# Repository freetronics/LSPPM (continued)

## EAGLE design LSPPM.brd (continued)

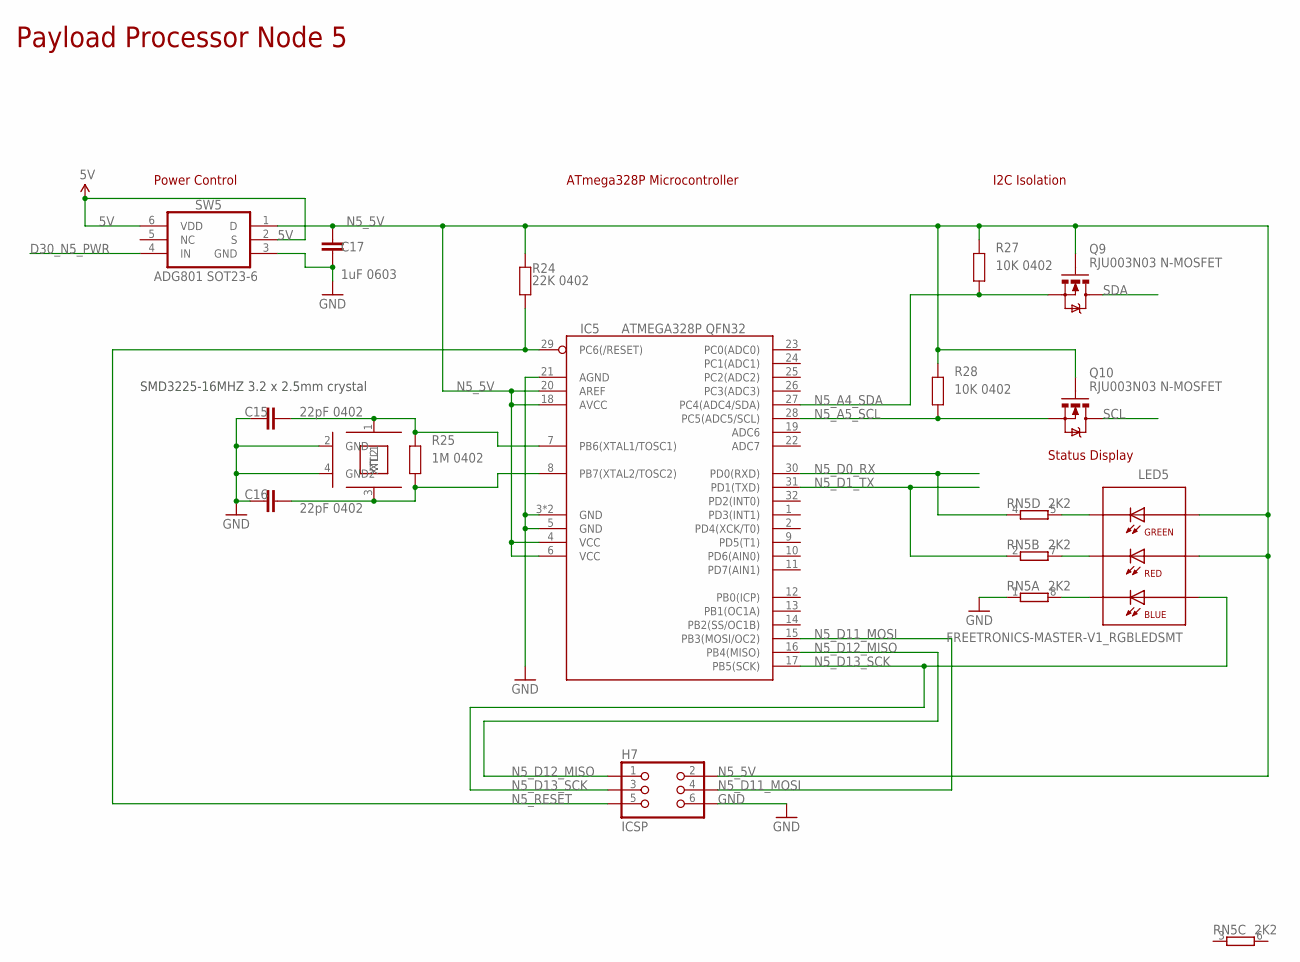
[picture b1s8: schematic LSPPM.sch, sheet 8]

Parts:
C15, C16: 22pF 0402; C0402
C17: 1uF 0603; C0603
H7: ICSP; M2X3-2MM
IC5: ATMEGA328P QFN32; MLF32
LED5: FREETRONICS-MASTER-V1_RGBLEDSMT; FREETRONICS-MASTER-V1_19-337
Q9, Q10: RJU003N03 N-MOSFET; SOT32-3
R24: 22K 0402; R0402
R25: 1M 0402; R0402
R27, R28: 10K 0402; R0402
RN5: 2K2; CAY16
SW5: ADG801 SOT23-6; SOT23-6
XTL5: SMD3225-16MHZ 3.2 x 2.5mm crystal; CRYSTAL-SMD-3X2

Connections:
5V: SW5.2 (S), SW5.6 (VDD); also elsewhere on the board
D30_N5_PWR: SW5.4 (IN); also elsewhere on the board
GND: C15.1, C16.1, C17.2, H7.6, IC5.3 (GND), IC5.5 (GND), IC5.21 (AGND), IC5.TGND (GND), RN5.1, SW5.3 (GND), XTL5.2 (GND), XTL5.4 (GND2); also elsewhere on the board
N5_5V: C17.1, H7.2, IC5.4 (VCC), IC5.6 (VCC), IC5.18 (AVCC), IC5.20 (AREF), LED5.5 (A-R), LED5.6 (A-G), Q9.1 (G), Q10.1 (G), R24.2, R27.2, R28.2, SW5.1 (D)
N5_A4_SDA: IC5.27 (PC4(ADC4/SDA)), Q9.2 (S), R27.1
N5_A5_SCL: IC5.28 (PC5(ADC5/SCL)), Q10.2 (S), R28.1
N5_D0_RX: IC5.30 (PD0(RXD)), RN5.4 (1); also elsewhere on the board
N5_D1_TX: IC5.31 (PD1(TXD)), RN5.2 (1); also elsewhere on the board
N5_D11_MOSI: H7.4, IC5.15 (PB3(MOSI/OC2))
N5_D12_MISO: H7.1, IC5.16 (PB4(MISO))
N5_D13_SCK: H7.3, IC5.17 (PB5(SCK)), LED5.4 (A-B)
N5_RESET: H7.5, IC5.29 (PC6(/RESET)), R24.1; also elsewhere on the board
unnamed: C16.2, IC5.8 (PB7(XTAL2/TOSC2)), R25.1, XTL5.3 (XTL2)
unnamed: C15.2, IC5.7 (PB6(XTAL1/TOSC1)), R25.2, XTL5.1 (XTL1)
unnamed: LED5.2 (C-R), RN5.7 (2)
unnamed: LED5.1 (C-B), RN5.8 (2)
unnamed: LED5.3 (C-G), RN5.5 (2)
SCL: Q10.3 (D); also elsewhere on the board
SDA: Q9.3 (D); also elsewhere on the board

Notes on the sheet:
Payload Processor Node 5
ATmega328P Microcontroller
I2C Isolation
Status Display
Power Control
SMD3225-16MHZ 3.2 x 2.5mm crystal

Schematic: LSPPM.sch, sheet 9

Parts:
C18, C19: 22pF 0402; C0402
C20: 1uF 0603; C0603
H8: ICSP; M2X3-2MM
IC6: ATMEGA328P QFN32; MLF32
LED6: FREETRONICS-MASTER-V1_RGBLEDSMT; FREETRONICS-MASTER-V1_19-337
Q13, Q14: RJU003N03 N-MOSFET; SOT32-3
R29: 22K 0402; R0402
R30: 1M 0402; R0402
R31, R34: 10K 0402; R0402
RN6: 2K2; CAY16
SW6: ADG801 SOT23-6; SOT23-6
XTL6: SMD3225-16MHZ 3.2 x 2.5mm crystal; CRYSTAL-SMD-3X2

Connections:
5V: SW6.2 (S), SW6.6 (VDD); also elsewhere on the board
D31_N6_PWR: SW6.4 (IN); also elsewhere on the board
GND: C18.1, C19.1, C20.2, H8.6, IC6.3 (GND), IC6.5 (GND), IC6.21 (AGND), IC6.TGND (GND), RN6.1, SW6.3 (GND), XTL6.2 (GND), XTL6.4 (GND2); also elsewhere on the board
N6_5V: C20.1, H8.2, IC6.4 (VCC), IC6.6 (VCC), IC6.18 (AVCC), IC6.20 (AREF), LED6.5 (A-R), LED6.6 (A-G), Q13.1 (G), Q14.1 (G), R29.2, R31.2, R34.2, SW6.1 (D)
N6_A4_SDA: IC6.27 (PC4(ADC4/SDA)), Q13.2 (S), R31.1
N6_A5_SCL: IC6.28 (PC5(ADC5/SCL)), Q14.2 (S), R34.1
N6_D0_RX: IC6.30 (PD0(RXD)), RN6.4 (1); also elsewhere on the board
N6_D1_TX: IC6.31 (PD1(TXD)), RN6.2 (1); also elsewhere on the board
N6_D11_MOSI: H8.4, IC6.15 (PB3(MOSI/OC2))
N6_D12_MISO: H8.1, IC6.16 (PB4(MISO))
N6_D13_SCK: H8.3, IC6.17 (PB5(SCK)), LED6.4 (A-B)
N6_RESET: H8.5, IC6.29 (PC6(/RESET)), R29.1; also elsewhere on the board
unnamed: C19.2, IC6.8 (PB7(XTAL2/TOSC2)), R30.1, XTL6.3 (XTL2)
unnamed: C18.2, IC6.7 (PB6(XTAL1/TOSC1)), R30.2, XTL6.1 (XTL1)
unnamed: LED6.2 (C-R), RN6.7 (2)
unnamed: LED6.1 (C-B), RN6.8 (2)
unnamed: LED6.3 (C-G), RN6.5 (2)
SCL: Q14.3 (D); also elsewhere on the board
SDA: Q13.3 (D); also elsewhere on the board

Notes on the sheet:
Payload Processor Node 6
ATmega328P Microcontroller
I2C Isolation
Status Display
Power Control
SMD3225-16MHZ 3.2 x 2.5mm crystal

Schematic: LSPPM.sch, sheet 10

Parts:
C21, C22: 22pF 0402; C0402
C23: 1uF 0603; C0603
H9: ICSP; M2X3-2MM
IC7: ATMEGA328P QFN32; MLF32
LED7: FREETRONICS-MASTER-V1_RGBLEDSMT; FREETRONICS-MASTER-V1_19-337
Q15, Q16: RJU003N03 N-MOSFET; SOT32-3
R35: 22K 0402; R0402
R36: 1M 0402; R0402
R37, R38: 10K 0402; R0402
RN7: 2K2; CAY16
SW7: ADG801 SOT23-6; SOT23-6
XTL7: SMD3225-16MHZ 3.2 x 2.5mm crystal; CRYSTAL-SMD-3X2

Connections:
5V: SW7.2 (S), SW7.6 (VDD); also elsewhere on the board
D32_N7_PWR: SW7.4 (IN); also elsewhere on the board
GND: C21.1, C22.1, C23.2, H9.6, IC7.3 (GND), IC7.5 (GND), IC7.21 (AGND), IC7.TGND (GND), RN7.1, SW7.3 (GND), XTL7.2 (GND), XTL7.4 (GND2); also elsewhere on the board
N7_5V: C23.1, H9.2, IC7.4 (VCC), IC7.6 (VCC), IC7.18 (AVCC), IC7.20 (AREF), LED7.5 (A-R), LED7.6 (A-G), Q15.1 (G), Q16.1 (G), R35.2, R37.2, R38.2, SW7.1 (D)
N7_A4_SDA: IC7.27 (PC4(ADC4/SDA)), Q15.2 (S), R37.1
N7_A5_SCL: IC7.28 (PC5(ADC5/SCL)), Q16.2 (S), R38.1
N7_D0_RX: IC7.30 (PD0(RXD)), RN7.4 (1); also elsewhere on the board
N7_D1_TX: IC7.31 (PD1(TXD)), RN7.2 (1); also elsewhere on the board
N7_D11_MOSI: H9.4, IC7.15 (PB3(MOSI/OC2))
N7_D12_MISO: H9.1, IC7.16 (PB4(MISO))
N7_D13_SCK: H9.3, IC7.17 (PB5(SCK)), LED7.4 (A-B)
N7_RESET: H9.5, IC7.29 (PC6(/RESET)), R35.1; also elsewhere on the board
unnamed: C22.2, IC7.8 (PB7(XTAL2/TOSC2)), R36.1, XTL7.3 (XTL2)
unnamed: C21.2, IC7.7 (PB6(XTAL1/TOSC1)), R36.2, XTL7.1 (XTL1)
unnamed: LED7.2 (C-R), RN7.7 (2)
unnamed: LED7.1 (C-B), RN7.8 (2)
unnamed: LED7.3 (C-G), RN7.5 (2)
SCL: Q16.3 (D); also elsewhere on the board
SDA: Q15.3 (D); also elsewhere on the board

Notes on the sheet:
Payload Processor Node 7
ATmega328P Microcontroller
I2C Isolation
Status Display
Power Control
SMD3225-16MHZ 3.2 x 2.5mm crystal

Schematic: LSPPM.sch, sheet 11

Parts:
C24, C25: 22pF 0402; C0402
C26: 1uF 0603; C0603
H10: ICSP; M2X3-2MM
IC8: ATMEGA328P QFN32; MLF32
LED8: FREETRONICS-MASTER-V1_RGBLEDSMT; FREETRONICS-MASTER-V1_19-337
Q17, Q18: RJU003N03 N-MOSFET; SOT32-3
R39: 22K 0402; R0402
R40: 1M 0402; R0402
R41, R42: 10K 0402; R0402
RN8: 2K2; CAY16
SW8: ADG801 SOT23-6; SOT23-6
XTL8: SMD3225-16MHZ 3.2 x 2.5mm crystal; CRYSTAL-SMD-3X2

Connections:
5V: SW8.2 (S), SW8.6 (VDD); also elsewhere on the board
D33_N8_PWR: SW8.4 (IN); also elsewhere on the board
GND: C24.1, C25.1, C26.2, H10.6, IC8.3 (GND), IC8.5 (GND), IC8.21 (AGND), IC8.TGND (GND), RN8.1, SW8.3 (GND), XTL8.2 (GND), XTL8.4 (GND2); also elsewhere on the board
N8_5V: C26.1, H10.2, IC8.4 (VCC), IC8.6 (VCC), IC8.18 (AVCC), IC8.20 (AREF), LED8.5 (A-R), LED8.6 (A-G), Q17.1 (G), Q18.1 (G), R39.2, R41.2, R42.2, SW8.1 (D)
N8_A4_SDA: IC8.27 (PC4(ADC4/SDA)), Q17.2 (S), R41.1
N8_A5_SCL: IC8.28 (PC5(ADC5/SCL)), Q18.2 (S), R42.1
N8_D0_RX: IC8.30 (PD0(RXD)), RN8.4 (1); also elsewhere on the board
N8_D1_TX: IC8.31 (PD1(TXD)), RN8.2 (1); also elsewhere on the board
N8_D11_MOSI: H10.4, IC8.15 (PB3(MOSI/OC2))
N8_D12_MISO: H10.1, IC8.16 (PB4(MISO))
N8_D13_SCK: H10.3, IC8.17 (PB5(SCK)), LED8.4 (A-B)
N8_RESET: H10.5, IC8.29 (PC6(/RESET)), R39.1; also elsewhere on the board
unnamed: C25.2, IC8.8 (PB7(XTAL2/TOSC2)), R40.1, XTL8.3 (XTL2)
unnamed: C24.2, IC8.7 (PB6(XTAL1/TOSC1)), R40.2, XTL8.1 (XTL1)
unnamed: LED8.2 (C-R), RN8.7 (2)
unnamed: LED8.1 (C-B), RN8.8 (2)
unnamed: LED8.3 (C-G), RN8.5 (2)
SCL: Q18.3 (D); also elsewhere on the board
SDA: Q17.3 (D); also elsewhere on the board

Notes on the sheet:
Payload Processor Node 8
ATmega328P Microcontroller
I2C Isolation
Status Display
Power Control
SMD3225-16MHZ 3.2 x 2.5mm crystal

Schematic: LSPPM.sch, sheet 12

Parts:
C27, C28: 22pF 0402; C0402
C29: 1uF 0603; C0603
H11: ICSP; M2X3-2MM
IC9: ATMEGA328P QFN32; MLF32
LED9: FREETRONICS-MASTER-V1_RGBLEDSMT; FREETRONICS-MASTER-V1_19-337
Q19, Q20: RJU003N03 N-MOSFET; SOT32-3
R43: 22K 0402; R0402
R44: 1M 0402; R0402
R45, R46: 10K 0402; R0402
RN9: 2K2; CAY16
SW9: ADG801 SOT23-6; SOT23-6
XTL9: SMD3225-16MHZ 3.2 x 2.5mm crystal; CRYSTAL-SMD-3X2

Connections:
5V: SW9.2 (S), SW9.6 (VDD); also elsewhere on the board
D26_N9_PWR: SW9.4 (IN); also elsewhere on the board
GND: C27.1, C28.1, C29.2, H11.6, IC9.3 (GND), IC9.5 (GND), IC9.21 (AGND), IC9.TGND (GND), RN9.1, SW9.3 (GND), XTL9.2 (GND), XTL9.4 (GND2); also elsewhere on the board
N9_5V: C29.1, H11.2, IC9.4 (VCC), IC9.6 (VCC), IC9.18 (AVCC), IC9.20 (AREF), LED9.5 (A-R), LED9.6 (A-G), Q19.1 (G), Q20.1 (G), R43.2, R45.2, R46.2, SW9.1 (D)
N9_A4_SDA: IC9.27 (PC4(ADC4/SDA)), Q19.2 (S), R45.1
N9_A5_SCL: IC9.28 (PC5(ADC5/SCL)), Q20.2 (S), R46.1
N9_D0_RX: IC9.30 (PD0(RXD)), RN9.4 (1); also elsewhere on the board
N9_D1_TX: IC9.31 (PD1(TXD)), RN9.2 (1); also elsewhere on the board
N9_D11_MOSI: H11.4, IC9.15 (PB3(MOSI/OC2))
N9_D12_MISO: H11.1, IC9.16 (PB4(MISO))
N9_D13_SCK: H11.3, IC9.17 (PB5(SCK)), LED9.4 (A-B)
N9_RESET: H11.5, IC9.29 (PC6(/RESET)), R43.1; also elsewhere on the board
unnamed: C28.2, IC9.8 (PB7(XTAL2/TOSC2)), R44.1, XTL9.3 (XTL2)
unnamed: C27.2, IC9.7 (PB6(XTAL1/TOSC1)), R44.2, XTL9.1 (XTL1)
unnamed: LED9.2 (C-R), RN9.7 (2)
unnamed: LED9.1 (C-B), RN9.8 (2)
unnamed: LED9.3 (C-G), RN9.5 (2)
SCL: Q20.3 (D); also elsewhere on the board
SDA: Q19.3 (D); also elsewhere on the board

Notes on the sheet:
Payload Processor Node 9
ATmega328P Microcontroller
I2C Isolation
Status Display
Power Control
SMD3225-16MHZ 3.2 x 2.5mm crystal

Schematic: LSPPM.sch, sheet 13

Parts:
C30, C31: 22pF 0402; C0402
C32: 1uF 0603; C0603
H12: ICSP; M2X3-2MM
IC10: ATMEGA328P QFN32; MLF32
LED10: FREETRONICS-MASTER-V1_RGBLEDSMT; FREETRONICS-MASTER-V1_19-337
Q21, Q22: RJU003N03 N-MOSFET; SOT32-3
R47: 22K 0402; R0402
R48: 1M 0402; R0402
R49, R50: 10K 0402; R0402
RN10: 2K2; CAY16
SW10: ADG801 SOT23-6; SOT23-6
XTL10: SMD3225-16MHZ 3.2 x 2.5mm crystal; CRYSTAL-SMD-3X2

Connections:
5V: SW10.2 (S), SW10.6 (VDD); also elsewhere on the board
D27_N10_PWR: SW10.4 (IN); also elsewhere on the board
GND: C30.1, C31.1, C32.2, H12.6, IC10.3 (GND), IC10.5 (GND), IC10.21 (AGND), IC10.TGND (GND), RN10.1, SW10.3 (GND), XTL10.2 (GND), XTL10.4 (GND2); also elsewhere on the board
N10_5V: C32.1, H12.2, IC10.4 (VCC), IC10.6 (VCC), IC10.18 (AVCC), IC10.20 (AREF), LED10.5 (A-R), LED10.6 (A-G), Q21.1 (G), Q22.1 (G), R47.2, R49.2, R50.2, SW10.1 (D)
N10_A4_SDA: IC10.27 (PC4(ADC4/SDA)), Q21.2 (S), R49.1
N10_A5_SCL: IC10.28 (PC5(ADC5/SCL)), Q22.2 (S), R50.1
N10_D0_RX: IC10.30 (PD0(RXD)), RN10.4 (1); also elsewhere on the board
N10_D1_TX: IC10.31 (PD1(TXD)), RN10.2 (1); also elsewhere on the board
N10_D11_MOSI: H12.4, IC10.15 (PB3(MOSI/OC2))
N10_D12_MISO: H12.1, IC10.16 (PB4(MISO))
N10_D13_SCK: H12.3, IC10.17 (PB5(SCK)), LED10.4 (A-B)
N10_RESET: H12.5, IC10.29 (PC6(/RESET)), R47.1; also elsewhere on the board
unnamed: C31.2, IC10.8 (PB7(XTAL2/TOSC2)), R48.1, XTL10.3 (XTL2)
unnamed: C30.2, IC10.7 (PB6(XTAL1/TOSC1)), R48.2, XTL10.1 (XTL1)
unnamed: LED10.2 (C-R), RN10.7 (2)
unnamed: LED10.1 (C-B), RN10.8 (2)
unnamed: LED10.3 (C-G), RN10.5 (2)
SCL: Q22.3 (D); also elsewhere on the board
SDA: Q21.3 (D); also elsewhere on the board

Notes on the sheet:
Payload Processor Node 10
ATmega328P Microcontroller
I2C Isolation
Status Display
Power Control
SMD3225-16MHZ 3.2 x 2.5mm crystal

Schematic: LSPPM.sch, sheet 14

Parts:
C33, C34: 22pF 0402; C0402
C35: 1uF 0603; C0603
H13: ICSP; M2X3-2MM
IC11: ATMEGA328P QFN32; MLF32
LED11: FREETRONICS-MASTER-V1_RGBLEDSMT; FREETRONICS-MASTER-V1_19-337
Q23, Q24: RJU003N03 N-MOSFET; SOT32-3
R51: 22K 0402; R0402
R52: 1M 0402; R0402
R53, R54: 10K 0402; R0402
RN11: 2K2; CAY16
SW11: ADG801 SOT23-6; SOT23-6
XTL11: SMD3225-16MHZ 3.2 x 2.5mm crystal; CRYSTAL-SMD-3X2

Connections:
5V: SW11.2 (S), SW11.6 (VDD); also elsewhere on the board
D28_N11_PWR: SW11.4 (IN); also elsewhere on the board
GND: C33.1, C34.1, C35.2, H13.6, IC11.3 (GND), IC11.5 (GND), IC11.21 (AGND), IC11.TGND (GND), RN11.1, SW11.3 (GND), XTL11.2 (GND), XTL11.4 (GND2); also elsewhere on the board
N11_5V: C35.1, H13.2, IC11.4 (VCC), IC11.6 (VCC), IC11.18 (AVCC), IC11.20 (AREF), LED11.5 (A-R), LED11.6 (A-G), Q23.1 (G), Q24.1 (G), R51.2, R53.2, R54.2, SW11.1 (D); also elsewhere on the board
N11_A4_SDA: IC11.27 (PC4(ADC4/SDA)), Q23.2 (S), R53.1
N11_A5_SCL: IC11.28 (PC5(ADC5/SCL)), Q24.2 (S), R54.1
N11_D0_RX: IC11.30 (PD0(RXD)), RN11.4 (1); also elsewhere on the board
N11_D1_TX: IC11.31 (PD1(TXD)), RN11.2 (1); also elsewhere on the board
N11_D6: IC11.10 (PD6(AIN0)); also elsewhere on the board
N11_D7: IC11.11 (PD7(AIN1)); also elsewhere on the board
N11_D11_MOSI: H13.4, IC11.15 (PB3(MOSI/OC2))
N11_D12_MISO: H13.1, IC11.16 (PB4(MISO))
N11_D13_SCK: H13.3, IC11.17 (PB5(SCK)), LED11.4 (A-B)
N11_RESET: H13.5, IC11.29 (PC6(/RESET)), R51.1; also elsewhere on the board
unnamed: C34.2, IC11.8 (PB7(XTAL2/TOSC2)), R52.1, XTL11.3 (XTL2)
unnamed: C33.2, IC11.7 (PB6(XTAL1/TOSC1)), R52.2, XTL11.1 (XTL1)
unnamed: LED11.2 (C-R), RN11.7 (2)
unnamed: LED11.1 (C-B), RN11.8 (2)
unnamed: LED11.3 (C-G), RN11.5 (2)
SCL: Q24.3 (D); also elsewhere on the board
SDA: Q23.3 (D); also elsewhere on the board

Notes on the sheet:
Payload Processor Node 11
ATmega328P Microcontroller
I2C Isolation
Status Display
Power Control
SMD3225-16MHZ 3.2 x 2.5mm crystal
Note: Node 11 is connected via serial level shifters to the GPS module

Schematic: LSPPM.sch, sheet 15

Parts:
C36, C37: 22pF 0402; C0402
C38: 1uF 0603; C0603
H14: ICSP; M2X3-2MM
IC12: ATMEGA328P QFN32; MLF32
LED12: FREETRONICS-MASTER-V1_RGBLEDSMT; FREETRONICS-MASTER-V1_19-337
Q25, Q26: RJU003N03 N-MOSFET; SOT32-3
R55: 22K 0402; R0402
R56: 1M 0402; R0402
R57, R58: 10K 0402; R0402
RN12: 2K2; CAY16
SW12: ADG801 SOT23-6; SOT23-6
XTL12: SMD3225-16MHZ 3.2 x 2.5mm crystal; CRYSTAL-SMD-3X2

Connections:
5V: SW12.2 (S), SW12.6 (VDD); also elsewhere on the board
D29_N12_PWR: SW12.4 (IN); also elsewhere on the board
GND: C36.1, C37.1, C38.2, H14.6, IC12.3 (GND), IC12.5 (GND), IC12.21 (AGND), IC12.TGND (GND), RN12.1, SW12.3 (GND), XTL12.2 (GND), XTL12.4 (GND2); also elsewhere on the board
N12_5V: C38.1, H14.2, IC12.4 (VCC), IC12.6 (VCC), IC12.18 (AVCC), IC12.20 (AREF), LED12.5 (A-R), LED12.6 (A-G), Q25.1 (G), Q26.1 (G), R55.2, R57.2, R58.2, SW12.1 (D)
N12_A4_SDA: IC12.27 (PC4(ADC4/SDA)), Q25.2 (S), R57.1
N12_A5_SCL: IC12.28 (PC5(ADC5/SCL)), Q26.2 (S), R58.1
N12_D0_RX: IC12.30 (PD0(RXD)), RN12.4 (1); also elsewhere on the board
N12_D1_TX: IC12.31 (PD1(TXD)), RN12.2 (1); also elsewhere on the board
N12_D11_MOSI: H14.4, IC12.15 (PB3(MOSI/OC2))
N12_D12_MISO: H14.1, IC12.16 (PB4(MISO))
N12_D13_SCK: H14.3, IC12.17 (PB5(SCK)), LED12.4 (A-B)
N12_RESET: H14.5, IC12.29 (PC6(/RESET)), R55.1; also elsewhere on the board
unnamed: C37.2, IC12.8 (PB7(XTAL2/TOSC2)), R56.1, XTL12.3 (XTL2)
unnamed: C36.2, IC12.7 (PB6(XTAL1/TOSC1)), R56.2, XTL12.1 (XTL1)
unnamed: LED12.2 (C-R), RN12.7 (2)
unnamed: LED12.1 (C-B), RN12.8 (2)
unnamed: LED12.3 (C-G), RN12.5 (2)
SCL: Q26.3 (D); also elsewhere on the board
SDA: Q25.3 (D); also elsewhere on the board

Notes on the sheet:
Payload Processor Node 12
ATmega328P Microcontroller
I2C Isolation
Status Display
Power Control
SMD3225-16MHZ 3.2 x 2.5mm crystal

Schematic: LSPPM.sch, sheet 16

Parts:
C41, C42: 22pF 0402; C0402
C43: 1uF 0603; C0603
H15: ICSP; M2X3-2MM
IC13: ATMEGA328P QFN32; MLF32
LED13: FREETRONICS-MASTER-V1_RGBLEDSMT; FREETRONICS-MASTER-V1_19-337
Q27, Q28: RJU003N03 N-MOSFET; SOT32-3
R60: 22K 0402; R0402
R61: 1M 0402; R0402
R62, R63: 10K 0402; R0402
RN13: 2K2; CAY16
SW13: ADG801 SOT23-6; SOT23-6
XTL13: SMD3225-16MHZ 3.2 x 2.5mm crystal; CRYSTAL-SMD-3X2

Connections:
5V: SW13.2 (S), SW13.6 (VDD); also elsewhere on the board
D22_N13_PWR: SW13.4 (IN); also elsewhere on the board
GND: C41.1, C42.1, C43.2, H15.6, IC13.3 (GND), IC13.5 (GND), IC13.21 (AGND), IC13.TGND (GND), RN13.1, SW13.3 (GND), XTL13.2 (GND), XTL13.4 (GND2); also elsewhere on the board
N13_5V: C43.1, H15.2, IC13.4 (VCC), IC13.6 (VCC), IC13.18 (AVCC), IC13.20 (AREF), LED13.5 (A-R), LED13.6 (A-G), Q27.1 (G), Q28.1 (G), R60.2, R62.2, R63.2, SW13.1 (D)
N13_A4_SDA: IC13.27 (PC4(ADC4/SDA)), Q27.2 (S), R62.1
N13_A5_SCL: IC13.28 (PC5(ADC5/SCL)), Q28.2 (S), R63.1
N13_D0_RX: IC13.30 (PD0(RXD)), RN13.4 (1); also elsewhere on the board
N13_D1_TX: IC13.31 (PD1(TXD)), RN13.2 (1); also elsewhere on the board
N13_D11_MOSI: H15.4, IC13.15 (PB3(MOSI/OC2))
N13_D12_MISO: H15.1, IC13.16 (PB4(MISO))
N13_D13_SCK: H15.3, IC13.17 (PB5(SCK)), LED13.4 (A-B)
N13_RESET: H15.5, IC13.29 (PC6(/RESET)), R60.1; also elsewhere on the board
unnamed: C42.2, IC13.8 (PB7(XTAL2/TOSC2)), R61.1, XTL13.3 (XTL2)
unnamed: C41.2, IC13.7 (PB6(XTAL1/TOSC1)), R61.2, XTL13.1 (XTL1)
unnamed: LED13.2 (C-R), RN13.7 (2)
unnamed: LED13.1 (C-B), RN13.8 (2)
unnamed: LED13.3 (C-G), RN13.5 (2)
SCL: Q28.3 (D); also elsewhere on the board
SDA: Q27.3 (D); also elsewhere on the board

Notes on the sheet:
Payload Processor Node 13
ATmega328P Microcontroller
I2C Isolation
Status Display
Power Control
SMD3225-16MHZ 3.2 x 2.5mm crystal

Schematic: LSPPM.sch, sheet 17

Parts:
C44, C45: 22pF 0402; C0402
C46: 1uF 0603; C0603
H16: ICSP; M2X3-2MM
IC14: ATMEGA328P QFN32; MLF32
LED14: FREETRONICS-MASTER-V1_RGBLEDSMT; FREETRONICS-MASTER-V1_19-337
Q29, Q30: RJU003N03 N-MOSFET; SOT32-3
R64: 22K 0402; R0402
R65: 1M 0402; R0402
R66, R67: 10K 0402; R0402
RN14: 2K2; CAY16
SW14: ADG801 SOT23-6; SOT23-6
XTL14: SMD3225-16MHZ 3.2 x 2.5mm crystal; CRYSTAL-SMD-3X2

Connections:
5V: SW14.2 (S), SW14.6 (VDD); also elsewhere on the board
D23_N14_PWR: SW14.4 (IN); also elsewhere on the board
GND: C44.1, C45.1, C46.2, H16.6, IC14.3 (GND), IC14.5 (GND), IC14.21 (AGND), IC14.TGND (GND), RN14.1, SW14.3 (GND), XTL14.2 (GND), XTL14.4 (GND2); also elsewhere on the board
N14_5V: C46.1, H16.2, IC14.4 (VCC), IC14.6 (VCC), IC14.18 (AVCC), IC14.20 (AREF), LED14.5 (A-R), LED14.6 (A-G), Q29.1 (G), Q30.1 (G), R64.2, R66.2, R67.2, SW14.1 (D)
N14_A4_SDA: IC14.27 (PC4(ADC4/SDA)), Q29.2 (S), R66.1
N14_A5_SCL: IC14.28 (PC5(ADC5/SCL)), Q30.2 (S), R67.1
N14_D0_RX: IC14.30 (PD0(RXD)), RN14.4 (1); also elsewhere on the board
N14_D1_TX: IC14.31 (PD1(TXD)), RN14.2 (1); also elsewhere on the board
N14_D11_MOSI: H16.4, IC14.15 (PB3(MOSI/OC2))
N14_D12_MISO: H16.1, IC14.16 (PB4(MISO))
N14_D13_SCK: H16.3, IC14.17 (PB5(SCK)), LED14.4 (A-B)
N14_RESET: H16.5, IC14.29 (PC6(/RESET)), R64.1; also elsewhere on the board
unnamed: C45.2, IC14.8 (PB7(XTAL2/TOSC2)), R65.1, XTL14.3 (XTL2)
unnamed: C44.2, IC14.7 (PB6(XTAL1/TOSC1)), R65.2, XTL14.1 (XTL1)
unnamed: LED14.2 (C-R), RN14.7 (2)
unnamed: LED14.1 (C-B), RN14.8 (2)
unnamed: LED14.3 (C-G), RN14.5 (2)
SCL: Q30.3 (D); also elsewhere on the board
SDA: Q29.3 (D); also elsewhere on the board

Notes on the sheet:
Payload Processor Node 14
ATmega328P Microcontroller
I2C Isolation
Status Display
Power Control
SMD3225-16MHZ 3.2 x 2.5mm crystal

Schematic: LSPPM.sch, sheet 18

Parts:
C47, C48: 22pF 0402; C0402
C49: 1uF 0603; C0603
H17: ICSP; M2X3-2MM
IC15: ATMEGA328P QFN32; MLF32
LED15: FREETRONICS-MASTER-V1_RGBLEDSMT; FREETRONICS-MASTER-V1_19-337
Q31, Q32: RJU003N03 N-MOSFET; SOT32-3
R68: 22K 0402; R0402
R69: 1M 0402; R0402
R70, R71: 10K 0402; R0402
RN15: 2K2; CAY16
SW15: ADG801 SOT23-6; SOT23-6
XTL15: SMD3225-16MHZ 3.2 x 2.5mm crystal; CRYSTAL-SMD-3X2

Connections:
5V: SW15.2 (S), SW15.6 (VDD); also elsewhere on the board
D24_N15_PWR: SW15.4 (IN); also elsewhere on the board
GND: C47.1, C48.1, C49.2, H17.6, IC15.3 (GND), IC15.5 (GND), IC15.21 (AGND), IC15.TGND (GND), RN15.1, SW15.3 (GND), XTL15.2 (GND), XTL15.4 (GND2); also elsewhere on the board
N15_5V: C49.1, H17.2, IC15.4 (VCC), IC15.6 (VCC), IC15.18 (AVCC), IC15.20 (AREF), LED15.5 (A-R), LED15.6 (A-G), Q31.1 (G), Q32.1 (G), R68.2, R70.2, R71.2, SW15.1 (D)
N15_A4_SDA: IC15.27 (PC4(ADC4/SDA)), Q31.2 (S), R70.1
N15_A5_SCL: IC15.28 (PC5(ADC5/SCL)), Q32.2 (S), R71.1
N15_D0_RX: IC15.30 (PD0(RXD)), RN15.4 (1); also elsewhere on the board
N15_D1_TX: IC15.31 (PD1(TXD)), RN15.2 (1); also elsewhere on the board
N15_D11_MOSI: H17.4, IC15.15 (PB3(MOSI/OC2))
N15_D12_MISO: H17.1, IC15.16 (PB4(MISO))
N15_D13_SCK: H17.3, IC15.17 (PB5(SCK)), LED15.4 (A-B)
N15_RESET: H17.5, IC15.29 (PC6(/RESET)), R68.1; also elsewhere on the board
unnamed: C48.2, IC15.8 (PB7(XTAL2/TOSC2)), R69.1, XTL15.3 (XTL2)
unnamed: C47.2, IC15.7 (PB6(XTAL1/TOSC1)), R69.2, XTL15.1 (XTL1)
unnamed: LED15.2 (C-R), RN15.7 (2)
unnamed: LED15.1 (C-B), RN15.8 (2)
unnamed: LED15.3 (C-G), RN15.5 (2)
SCL: Q32.3 (D); also elsewhere on the board
SDA: Q31.3 (D); also elsewhere on the board

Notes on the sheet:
Payload Processor Node 15
ATmega328P Microcontroller
I2C Isolation
Status Display
Power Control
SMD3225-16MHZ 3.2 x 2.5mm crystal

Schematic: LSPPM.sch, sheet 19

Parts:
C50, C56: 22pF 0402; C0402
C57: 1uF 0603; C0603
H18: ICSP; M2X3-2MM
IC16: ATMEGA328P QFN32; MLF32
LED16: FREETRONICS-MASTER-V1_RGBLEDSMT; FREETRONICS-MASTER-V1_19-337
Q33, Q34: RJU003N03 N-MOSFET; SOT32-3
R72: 22K 0402; R0402
R73: 1M 0402; R0402
R74, R76: 10K 0402; R0402
RN16: 2K2; CAY16
SW16: ADG801 SOT23-6; SOT23-6
XTL16: SMD3225-16MHZ 3.2 x 2.5mm crystal; CRYSTAL-SMD-3X2

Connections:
5V: SW16.2 (S), SW16.6 (VDD); also elsewhere on the board
D25_N16_PWR: SW16.4 (IN); also elsewhere on the board
GND: C50.1, C56.1, C57.2, H18.6, IC16.3 (GND), IC16.5 (GND), IC16.21 (AGND), IC16.TGND (GND), RN16.1, SW16.3 (GND), XTL16.2 (GND), XTL16.4 (GND2); also elsewhere on the board
N16_5V: C57.1, H18.2, IC16.4 (VCC), IC16.6 (VCC), IC16.18 (AVCC), IC16.20 (AREF), LED16.5 (A-R), LED16.6 (A-G), Q33.1 (G), Q34.1 (G), R72.2, R74.2, R76.2, SW16.1 (D)
N16_A4_SDA: IC16.27 (PC4(ADC4/SDA)), Q33.2 (S), R74.1
N16_A5_SCL: IC16.28 (PC5(ADC5/SCL)), Q34.2 (S), R76.1
N16_D0_RX: IC16.30 (PD0(RXD)), RN16.4 (1); also elsewhere on the board
N16_D1_TX: IC16.31 (PD1(TXD)), RN16.2 (1); also elsewhere on the board
N16_D11_MOSI: H18.4, IC16.15 (PB3(MOSI/OC2))
N16_D12_MISO: H18.1, IC16.16 (PB4(MISO))
N16_D13_SCK: H18.3, IC16.17 (PB5(SCK)), LED16.4 (A-B)
N16_RESET: H18.5, IC16.29 (PC6(/RESET)), R72.1; also elsewhere on the board
unnamed: C56.2, IC16.8 (PB7(XTAL2/TOSC2)), R73.1, XTL16.3 (XTL2)
unnamed: C50.2, IC16.7 (PB6(XTAL1/TOSC1)), R73.2, XTL16.1 (XTL1)
unnamed: LED16.2 (C-R), RN16.7 (2)
unnamed: LED16.1 (C-B), RN16.8 (2)
unnamed: LED16.3 (C-G), RN16.5 (2)
SCL: Q34.3 (D); also elsewhere on the board
SDA: Q33.3 (D); also elsewhere on the board

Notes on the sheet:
Payload Processor Node 16
ATmega328P Microcontroller
I2C Isolation
Status Display
Power Control
SMD3225-16MHZ 3.2 x 2.5mm crystal

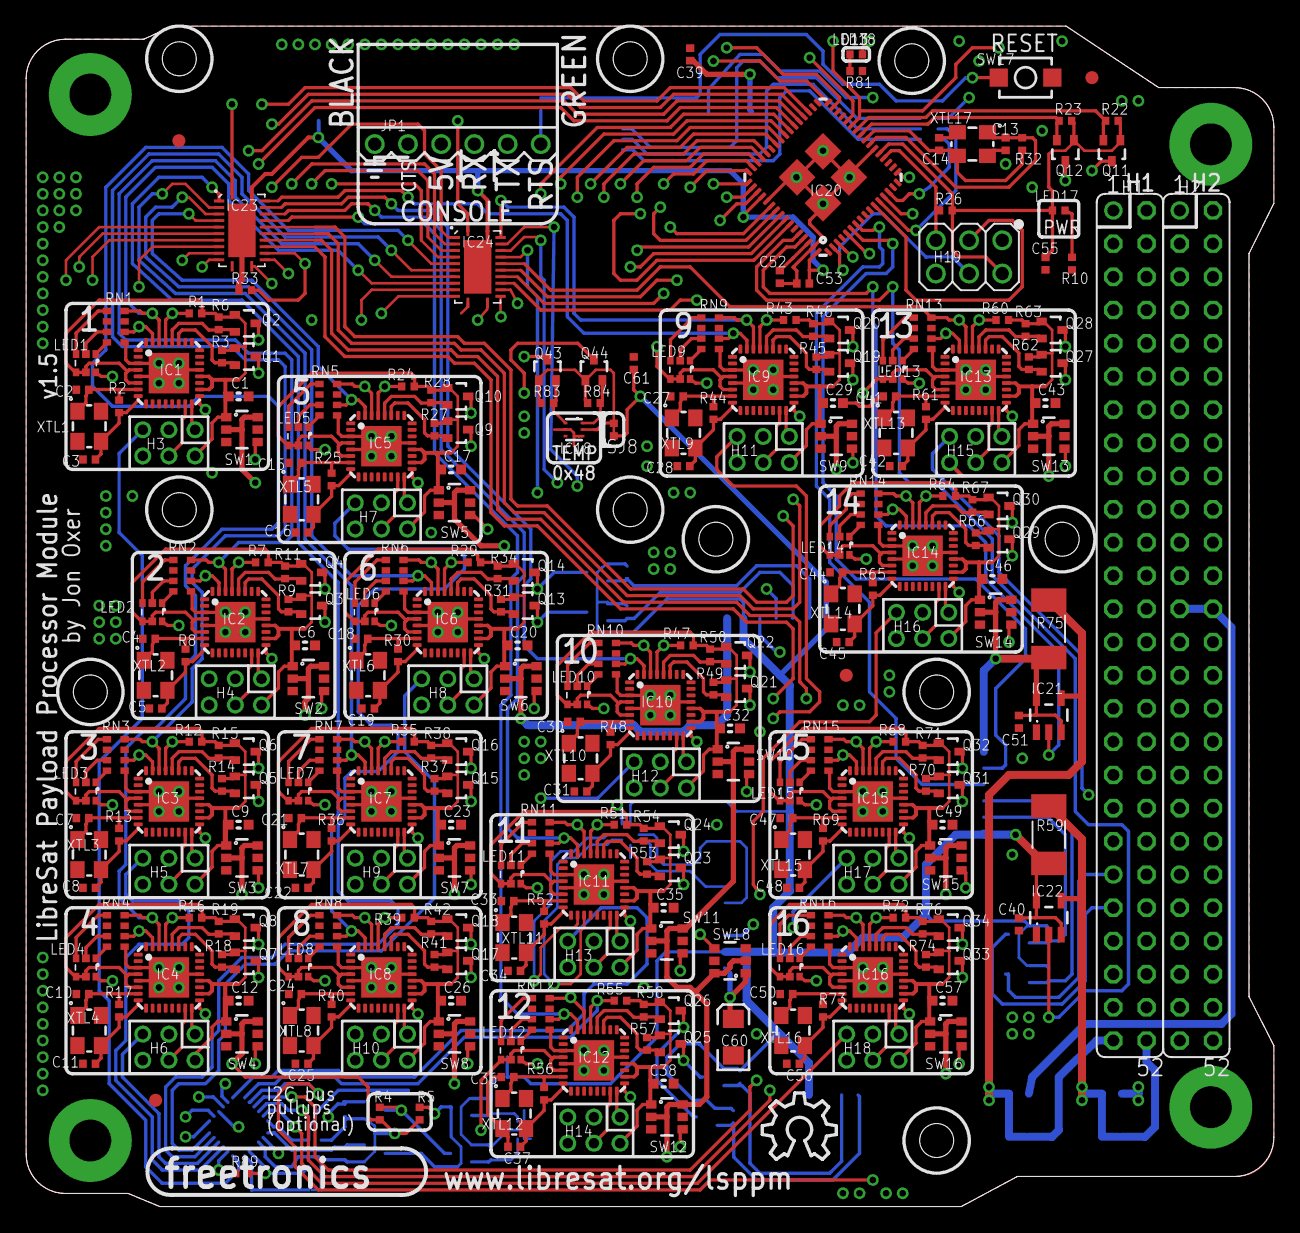
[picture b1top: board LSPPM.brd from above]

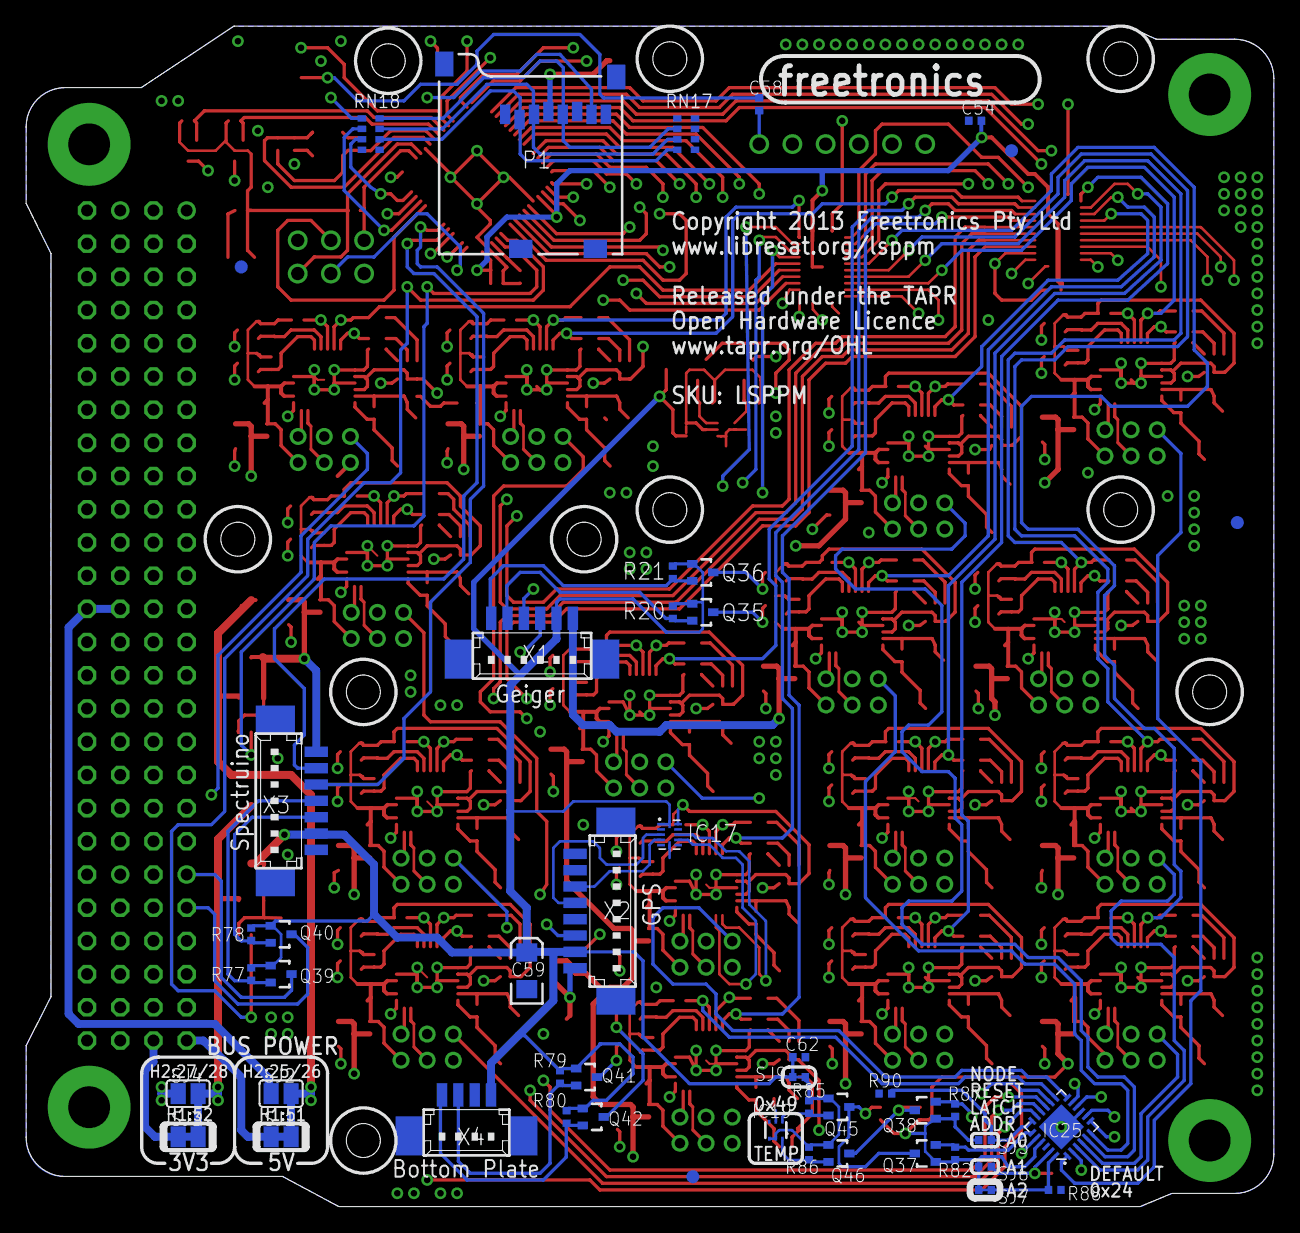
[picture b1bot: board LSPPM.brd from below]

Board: 4 copper layers, 95.5 x 90.3 mm, 341 parts (48 on the bottom side), 306 nets.

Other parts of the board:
U$33: OSHW_10X200_NOTEXT
